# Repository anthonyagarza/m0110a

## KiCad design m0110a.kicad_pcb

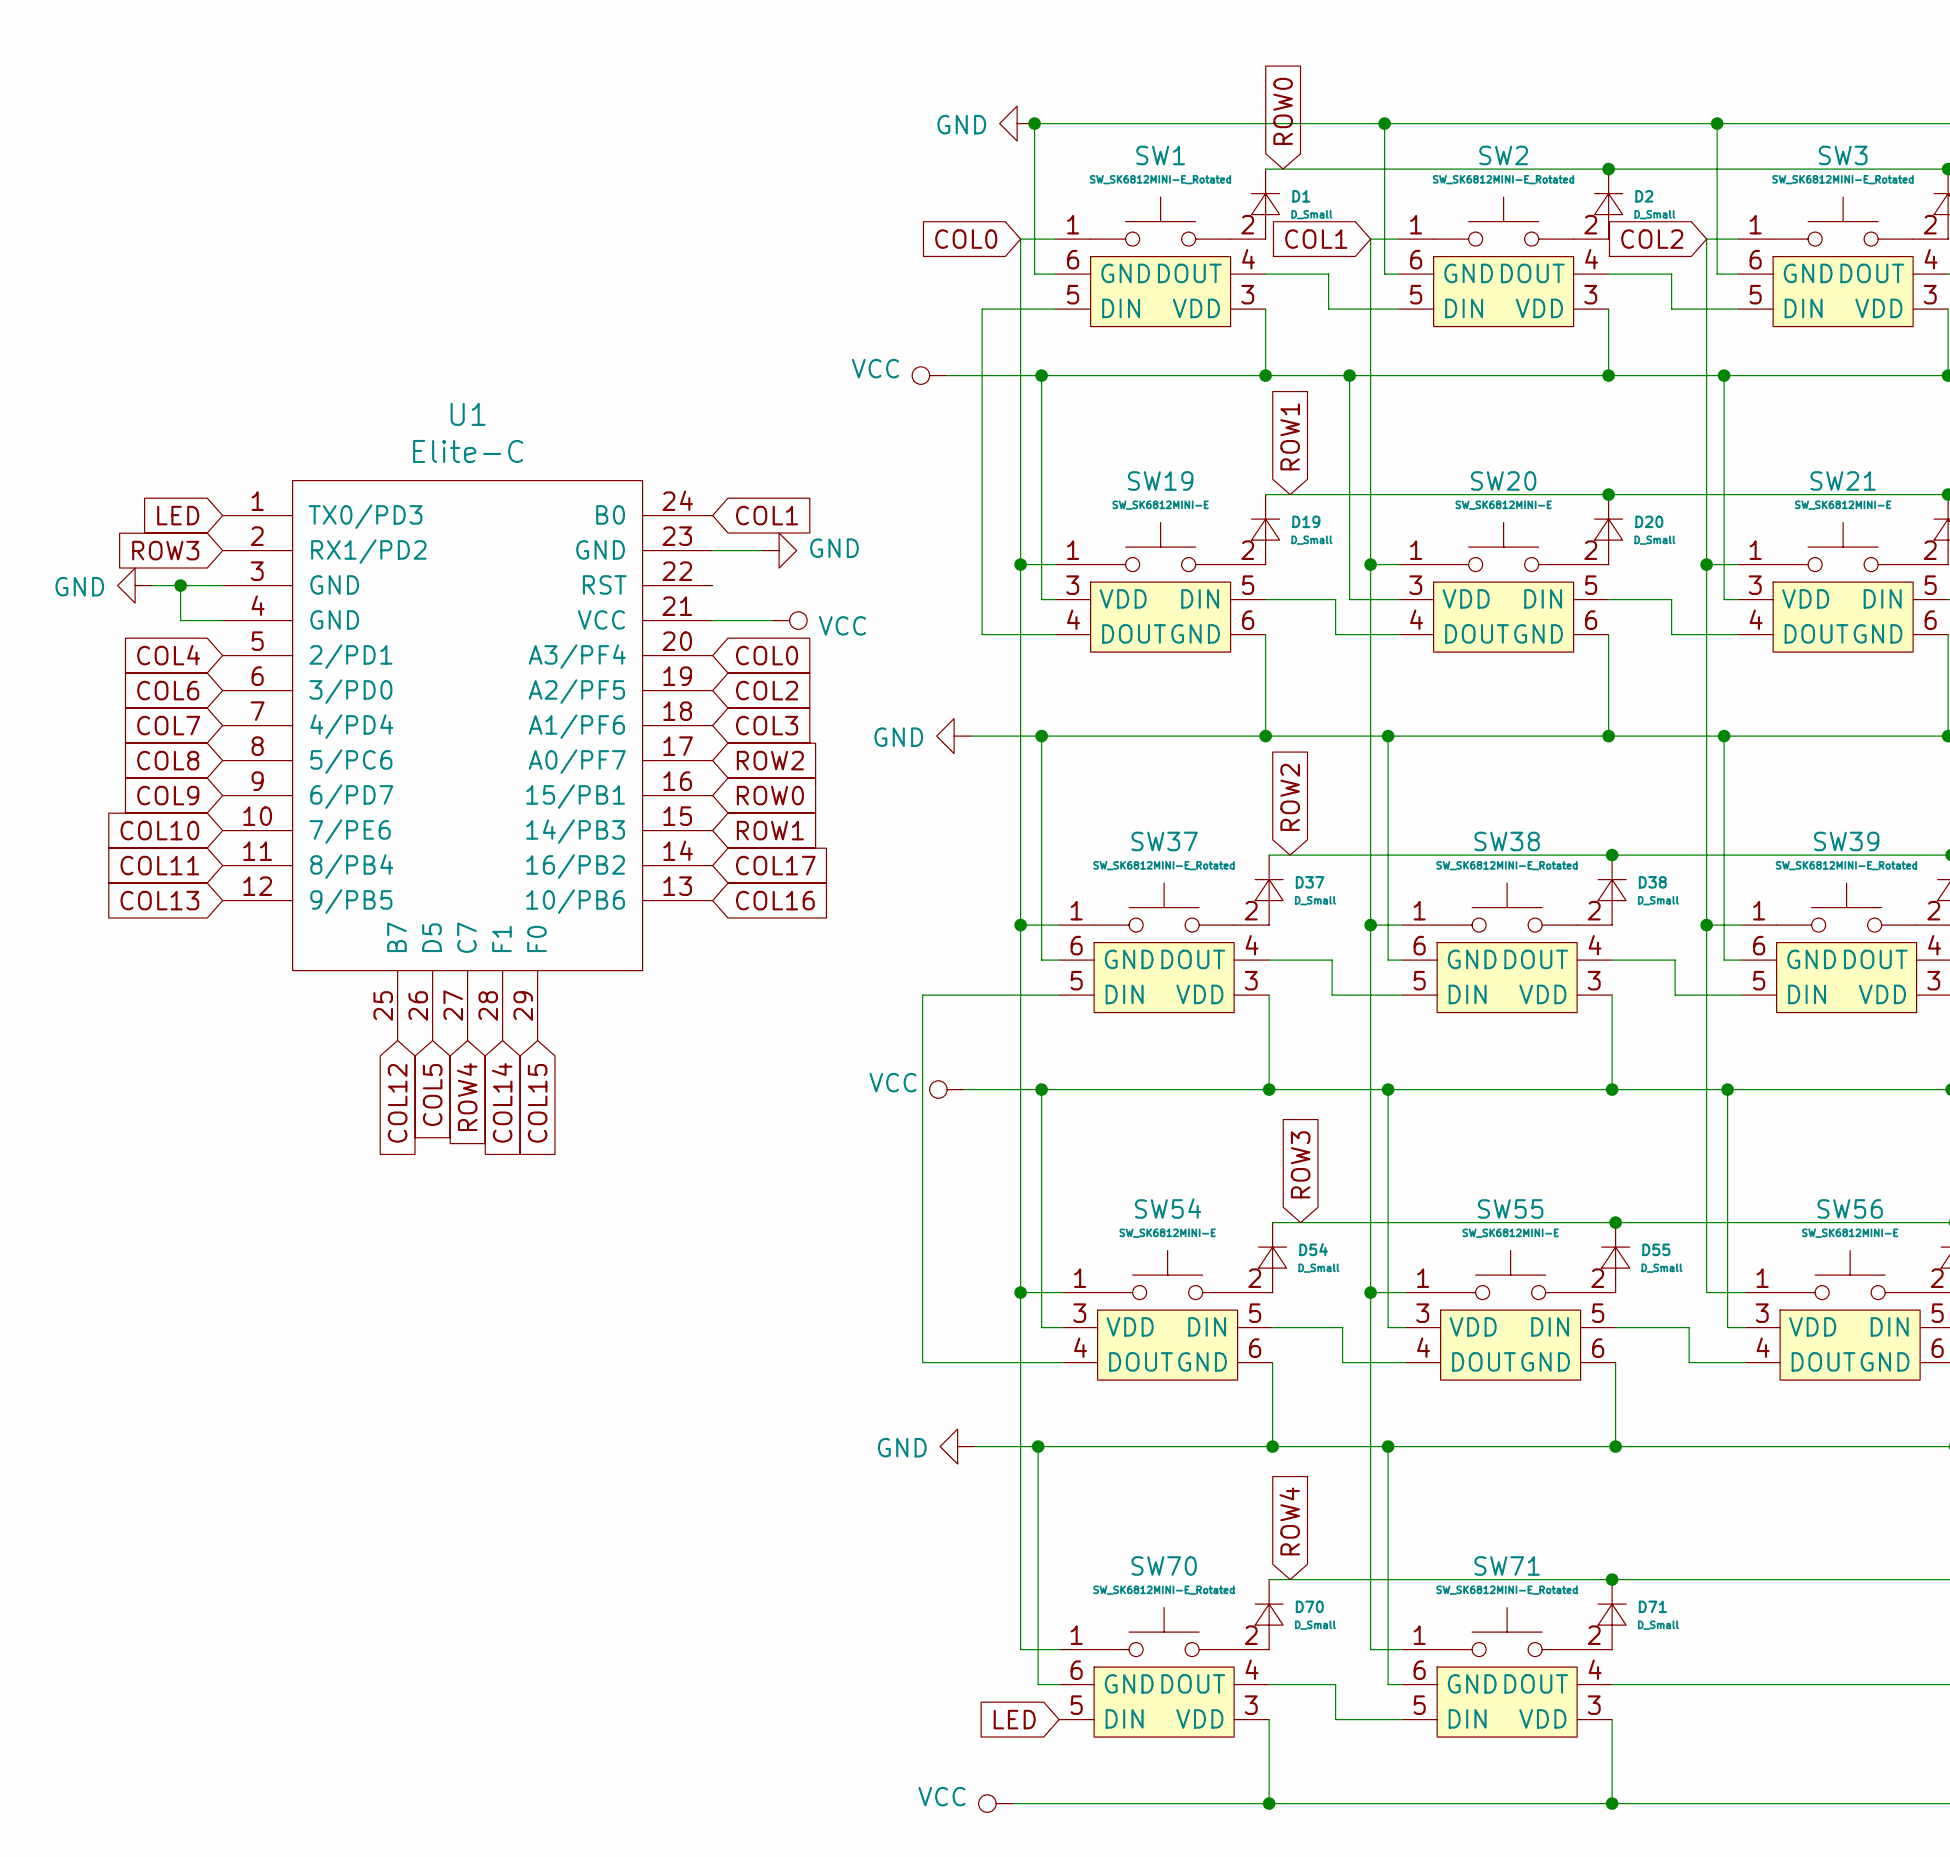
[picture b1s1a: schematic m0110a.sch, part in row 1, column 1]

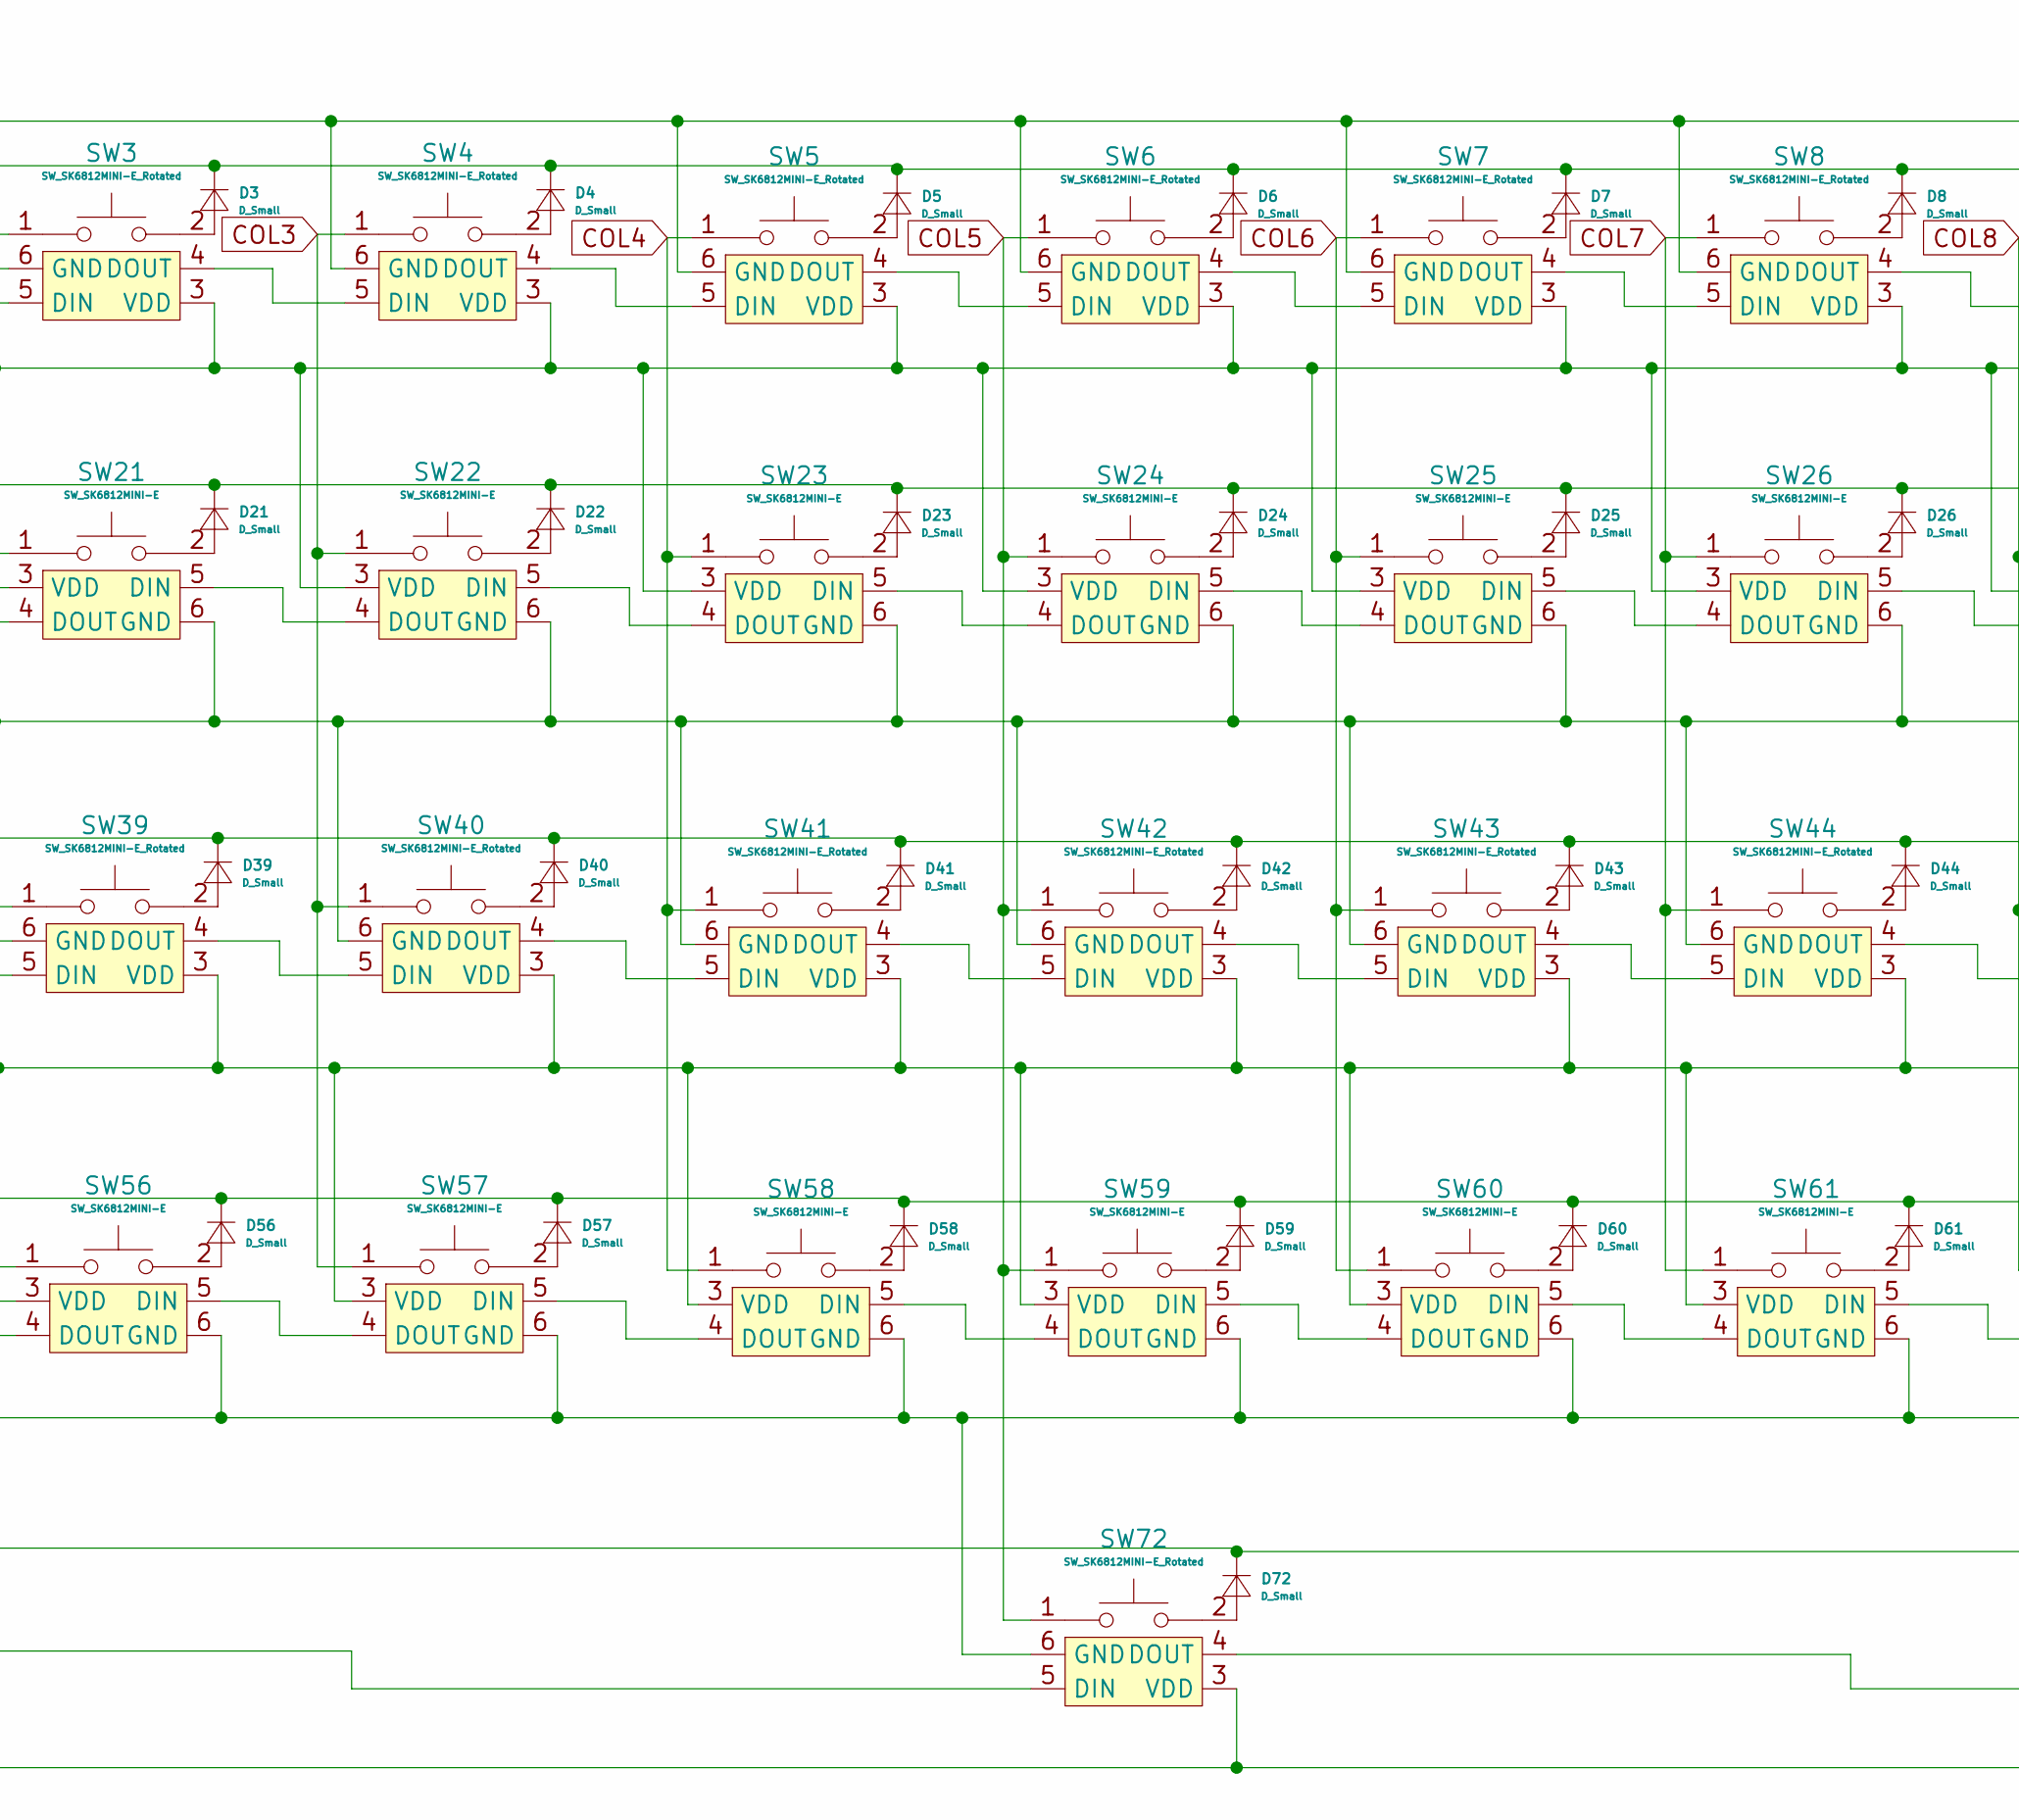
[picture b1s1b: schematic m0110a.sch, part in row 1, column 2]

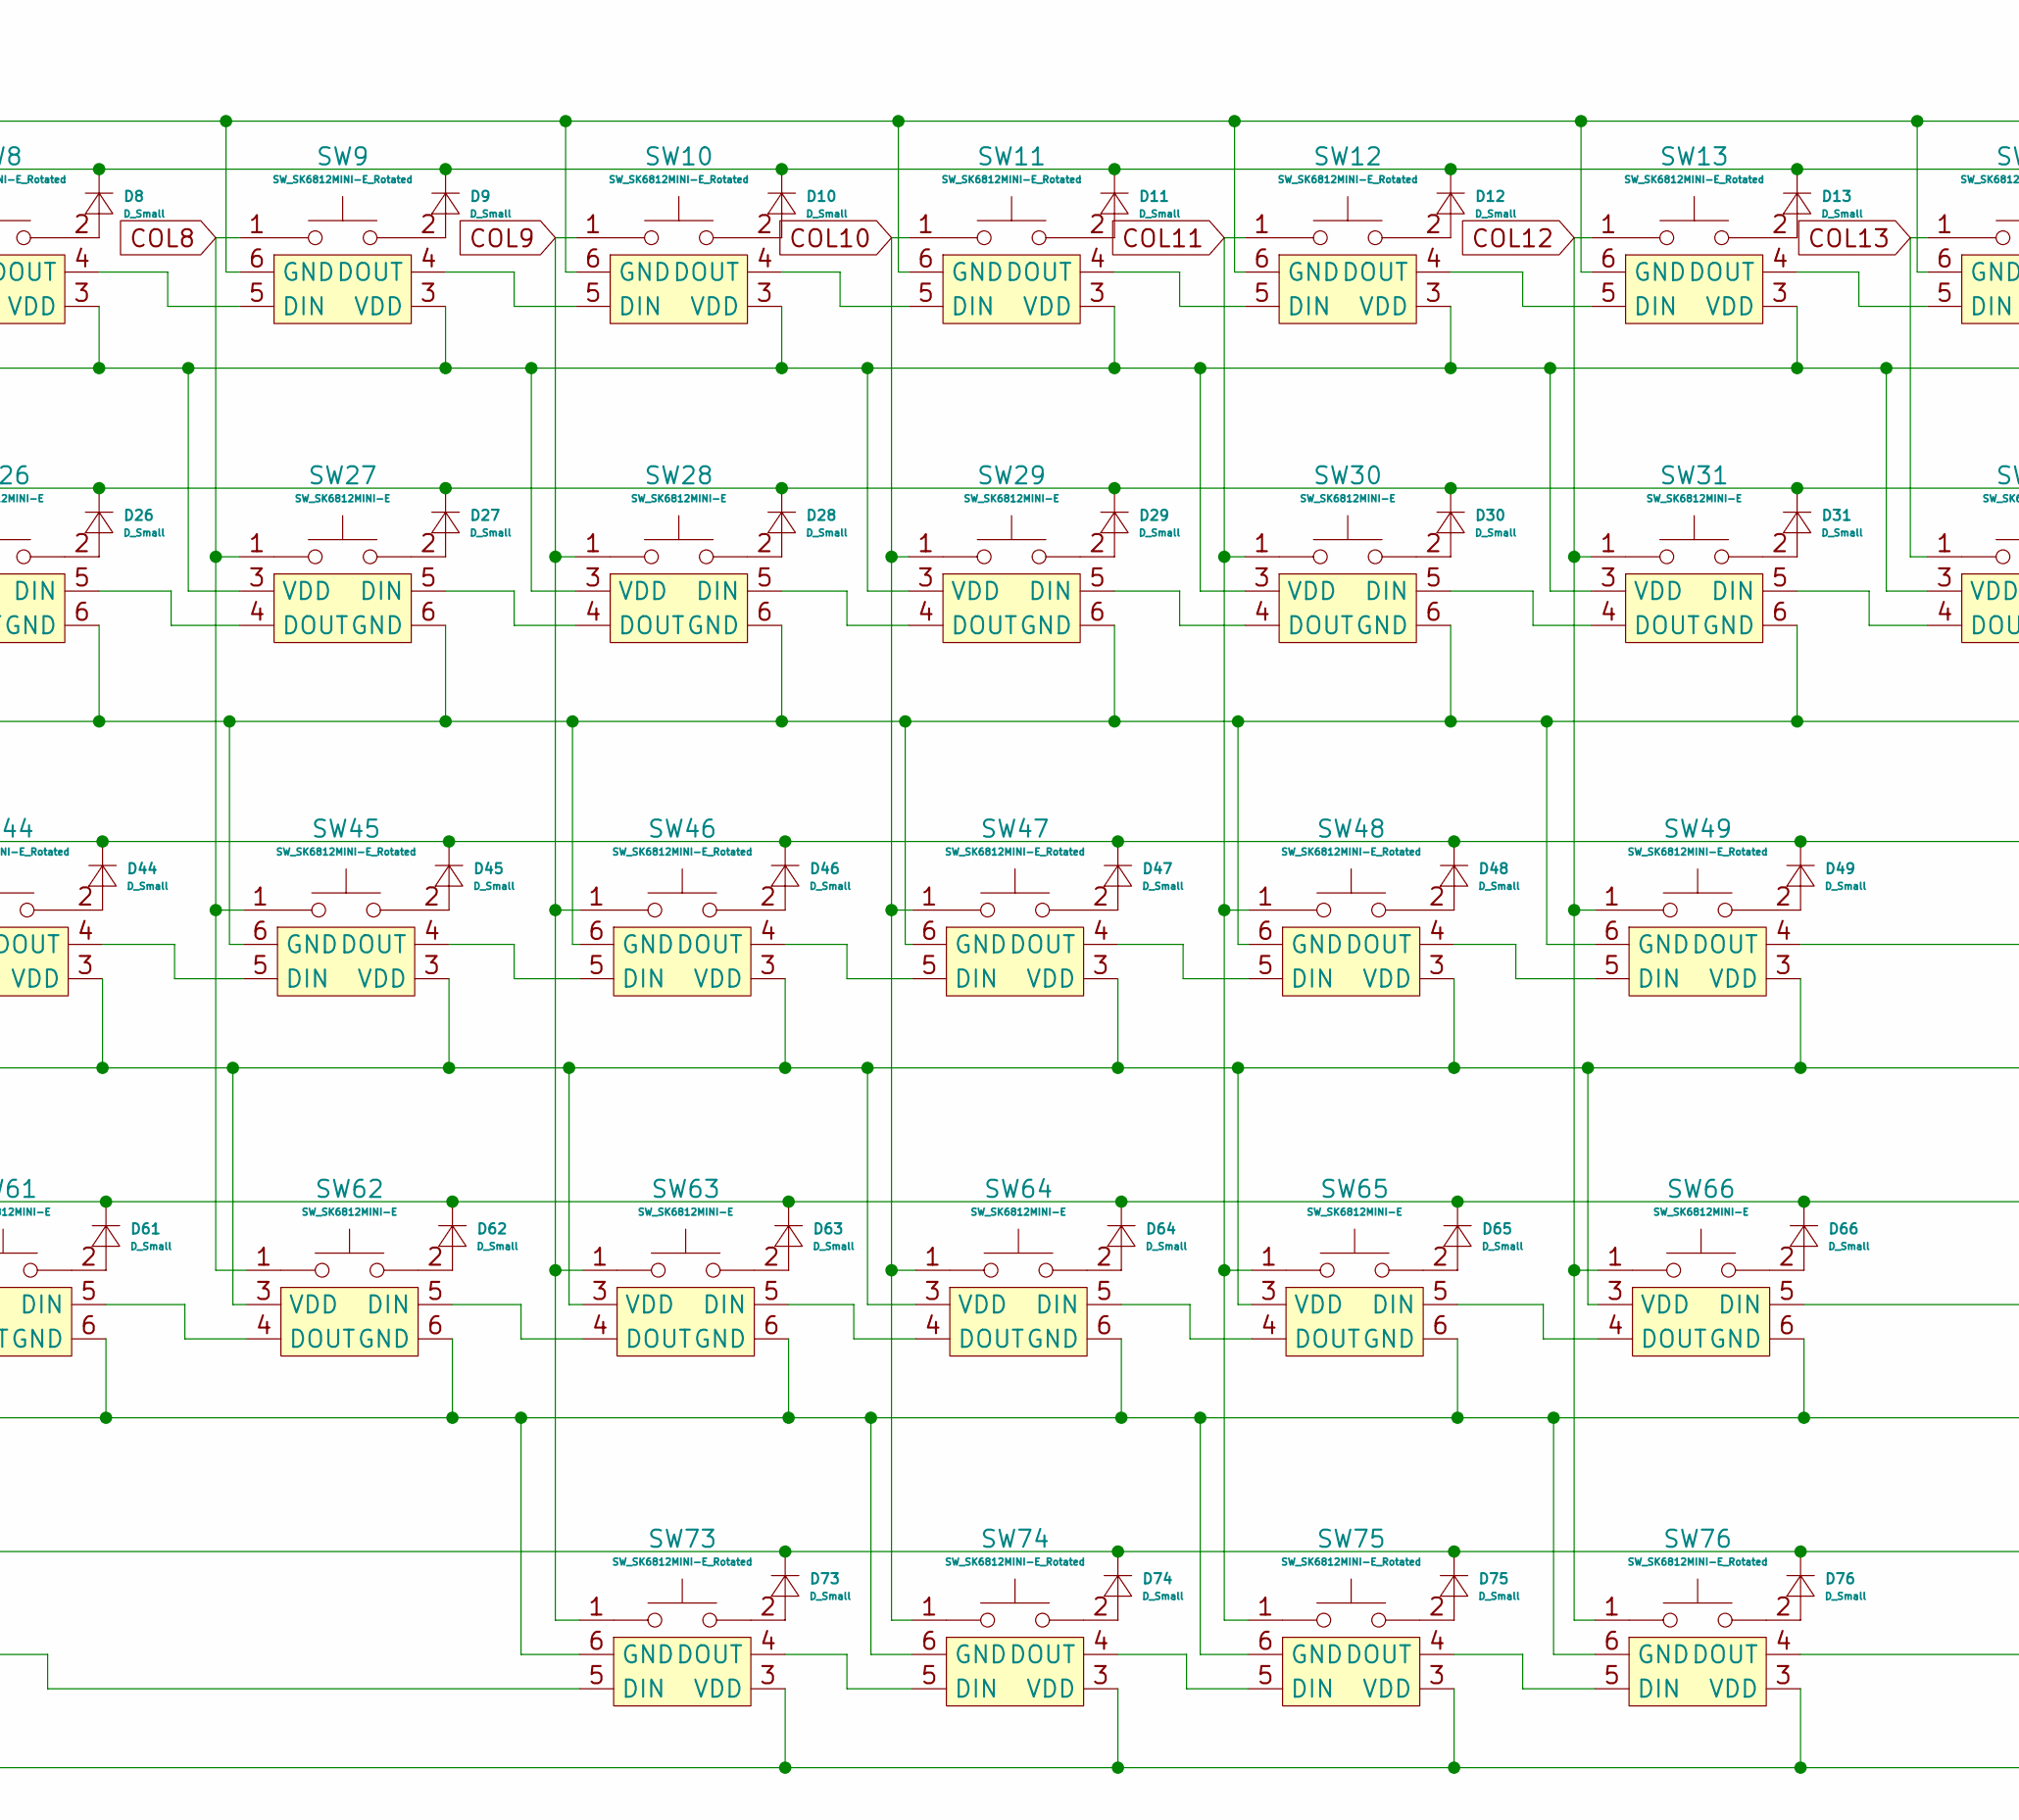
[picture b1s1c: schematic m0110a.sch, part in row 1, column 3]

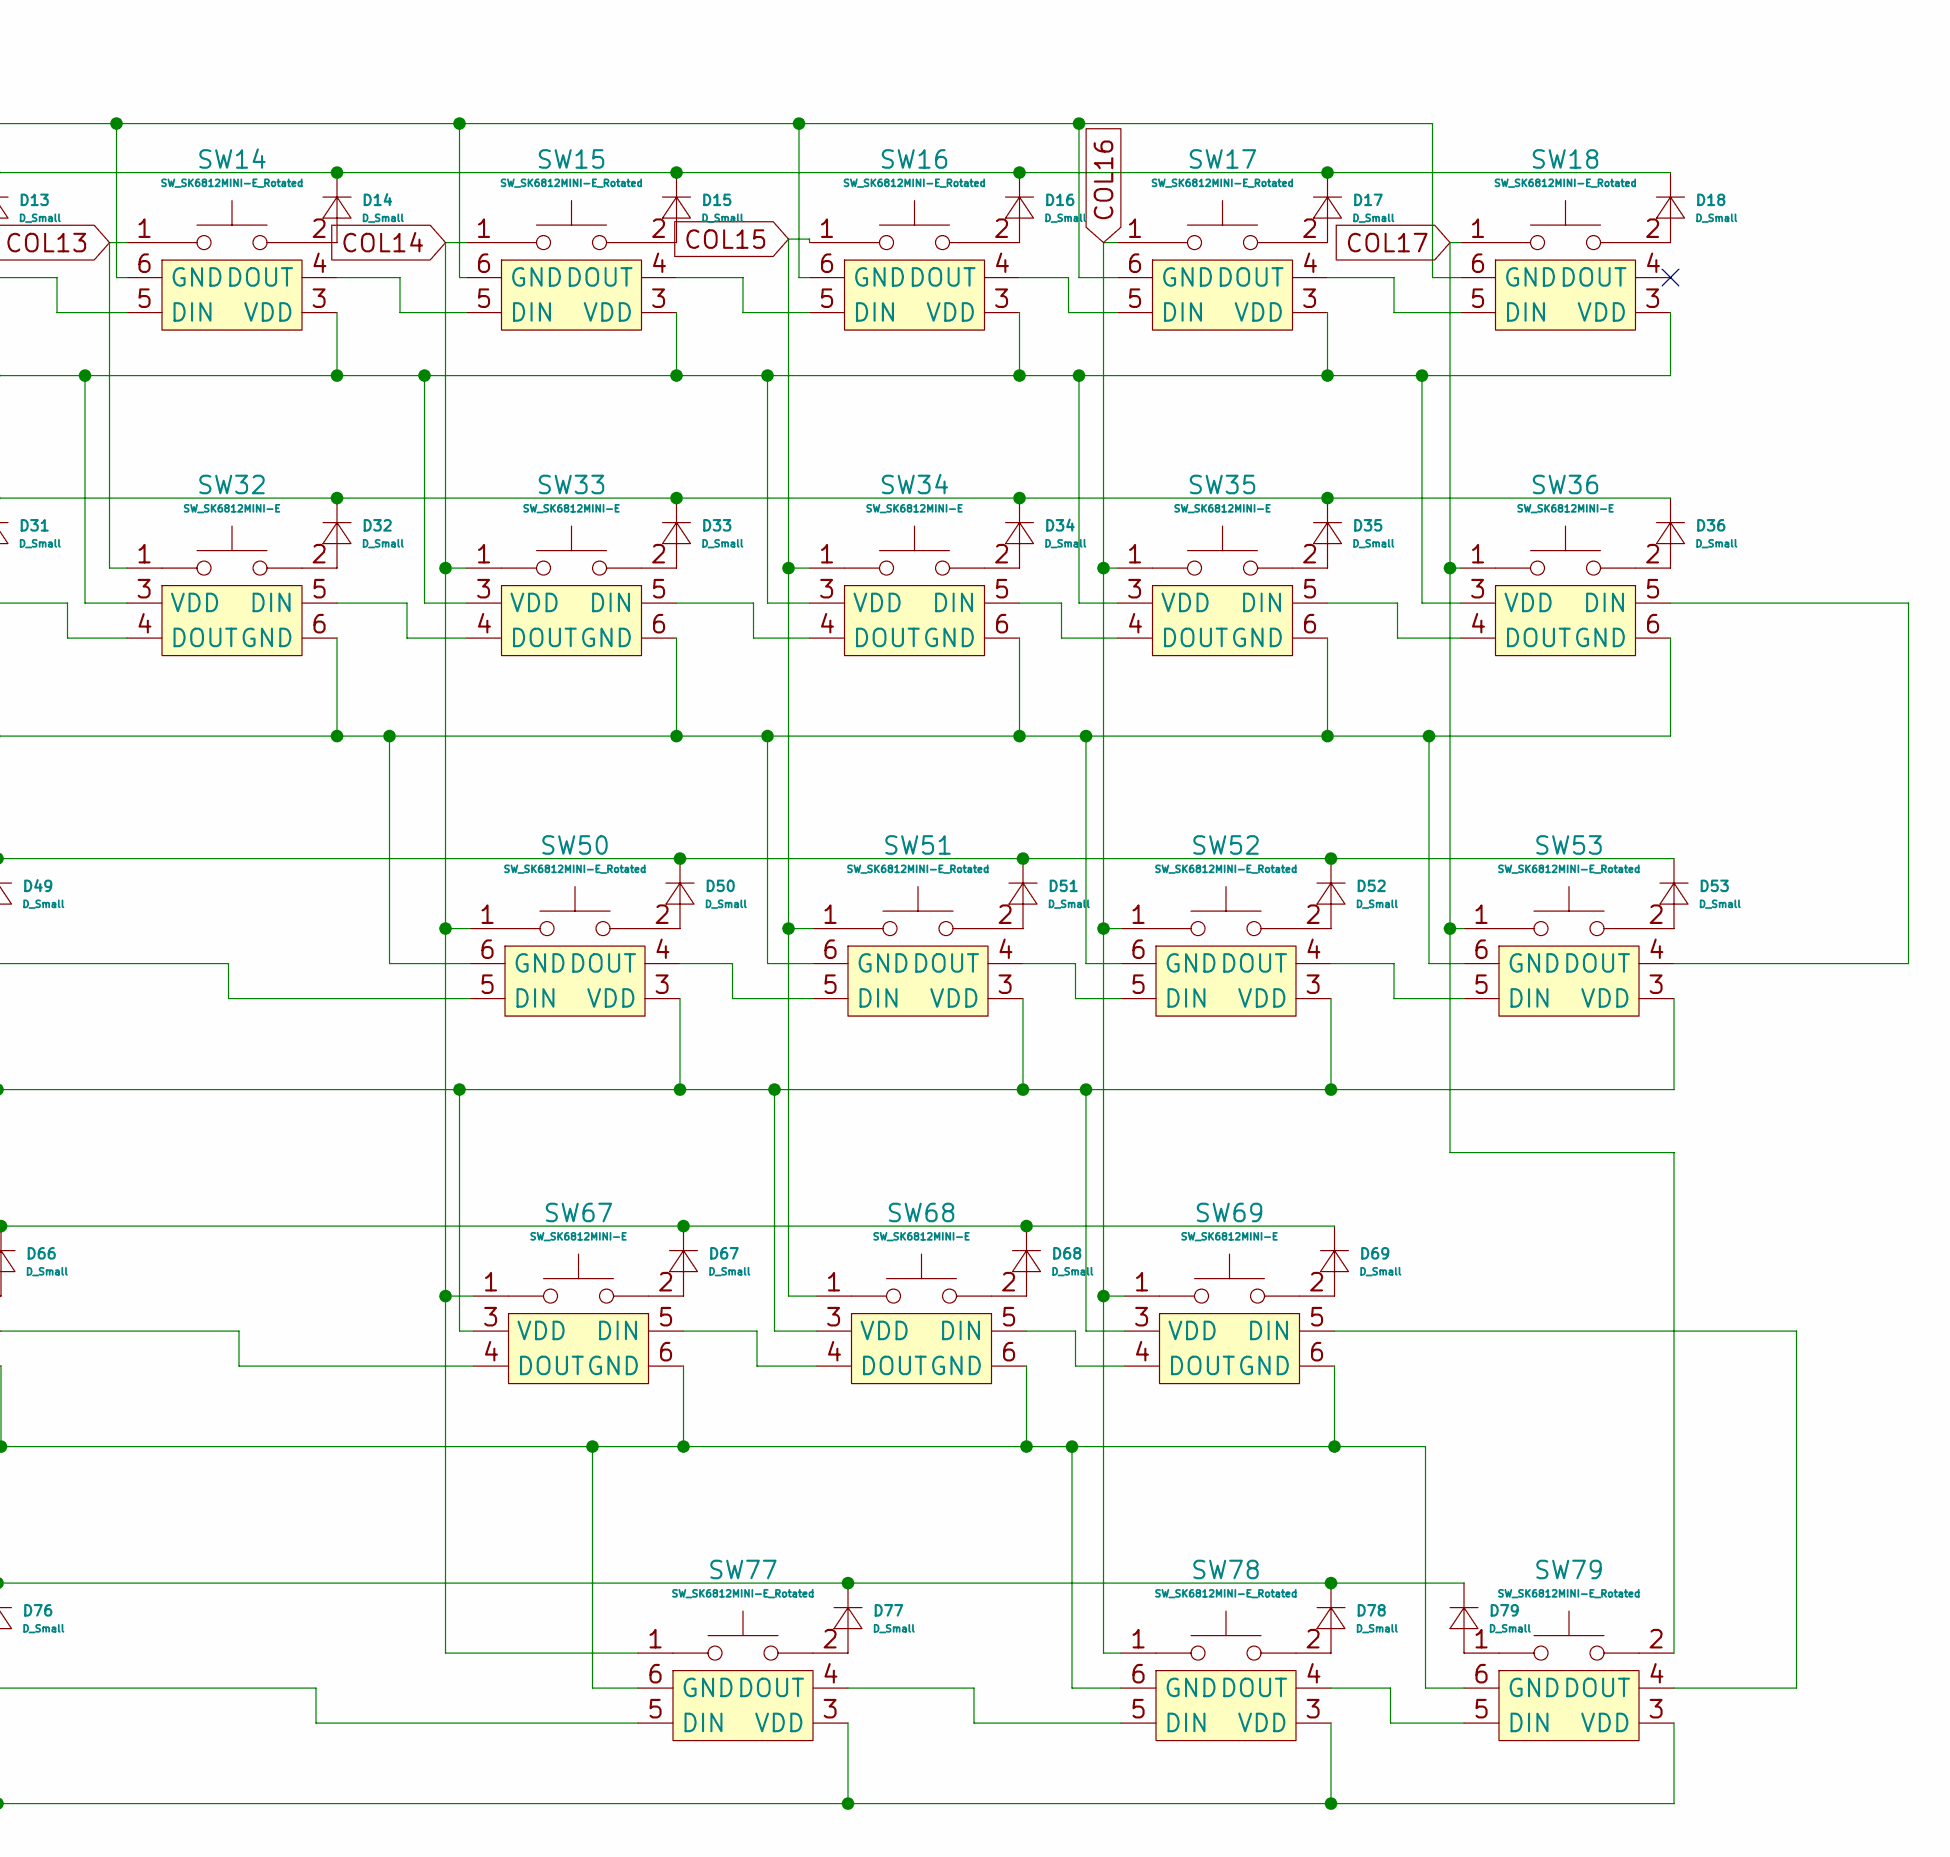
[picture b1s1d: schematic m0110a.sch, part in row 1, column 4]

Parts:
D1, D2, D3, D4, D5, D6, D7, D8, D9, D10, D11, D12, D13, D14, D15, D16, D17, D18, D19, D20, D21, D22, D23, D24, D25, D26, D27, D28, D29, D30, D31, D32, D33, D34, D35, D36, D37, D38, D39, D40, D41, D42, D43, D44, D45, D46, D47, D48, D49, D50, D51, D52, D53, D54, D55, D56, D57, D58, D59, D60, D61, D62, D63, D64, D65, D66, D67, D68, D69, D70, D71, D72, D73, D74, D75, D76, D77, D78, D79: D_Small; Diode
SW1, SW2, SW3, SW4, SW5, SW6, SW7, SW8, SW9, SW10, SW11, SW12, SW13, SW15, SW16, SW17, SW18, SW38, SW39, SW40, SW41, SW42, SW43, SW44, SW45, SW46, SW47, SW48, SW50, SW51, SW52, SW53, SW73, SW74, SW75, SW76, SW78: SW_SK6812MINI-E_Rotated; CherryMX_1.00u_PCB_KailhSocket_LTST-A683CEGBW-Rotated
SW14: SW_SK6812MINI-E_Rotated; CherryMX_1.50u_PCB_KailhSocket_LTST-A683CEGBW-Rotated
SW19: SW_SK6812MINI-E; CherryMX_1.50u_PCB_KailhSocket_LTST-A683CEGBW
SW20, SW21, SW22, SW23, SW24, SW25, SW26, SW27, SW28, SW29, SW30, SW31, SW32, SW33, SW34, SW35, SW36, SW55, SW56, SW57, SW58, SW59, SW60, SW61, SW62, SW63, SW64, SW66, SW67, SW68, SW69: SW_SK6812MINI-E; CherryMX_1.00u_PCB_KailhSocket_LTST-A683CEGBW
SW37, SW49: SW_SK6812MINI-E_Rotated; CherryMX_1.75u_PCB_KailhSocket_LTST-A683CEGBW-Rotated
SW54: SW_SK6812MINI-E; CherryMX_2.25u_PCB_KailhSocket_StabWireBottom_LTST-A683CEGBW
SW65: SW_SK6812MINI-E; CherryMX_1.25u_PCB_KailhSocket_LTST-A683CEGBW
SW70: SW_SK6812MINI-E_Rotated; CherryMX_1.50u_PCB_KailhSocket_LTST-A683CEGBW
SW71, SW77, SW79: SW_SK6812MINI-E_Rotated; CherryMX_2.00u_PCB_KailhSocket_StabWireBottom_LTST-A683CEGB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
SW72: SW_SK6812MINI-E_Rotated; CherryMX_7.00u_PCB_KailhSocket_StabWireBottom_LTST-A683CEGB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
U1: Elite-C

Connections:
COL0: SW1.1, SW19.1, SW37.1, SW54.1, SW70.1, U1.20 (A3/PF4)
COL1: SW2.1, SW20.1, SW38.1, SW55.1, SW71.1, U1.24 (B0)
COL2: SW3.1, SW21.1, SW39.1, SW56.1, U1.19 (A2/PF5)
COL3: SW4.1, SW22.1, SW40.1, SW57.1, U1.18 (A1/PF6)
COL4: SW5.1, SW23.1, SW41.1, SW58.1, U1.5 (2/PD1)
COL5: SW6.1, SW24.1, SW42.1, SW59.1, SW72.1, U1.26 (D5)
COL6: SW7.1, SW25.1, SW43.1, SW60.1, U1.6 (3/PD0)
COL7: SW8.1, SW26.1, SW44.1, SW61.1, U1.7 (4/PD4)
COL8: SW9.1, SW27.1, SW45.1, SW62.1, U1.8 (5/PC6)
COL9: SW10.1, SW28.1, SW46.1, SW63.1, SW73.1, U1.9 (6/PD7)
COL10: SW11.1, SW29.1, SW47.1, SW64.1, SW74.1, U1.10 (7/PE6)
COL11: SW12.1, SW30.1, SW48.1, SW65.1, SW75.1, U1.11 (8/PB4)
COL12: SW13.1, SW31.1, SW49.1, SW66.1, SW76.1, U1.25 (B7)
COL13: SW14.1, SW32.1, U1.12 (9/PB5)
COL14: SW15.1, SW33.1, SW50.1, SW67.1, SW77.1, U1.28 (F1)
COL15: SW16.1, SW34.1, SW51.1, SW68.1, U1.29 (F0)
COL16: SW17.1, SW35.1, SW52.1, SW69.1, SW78.1, U1.13 (10/PB6)
COL17: SW18.1, SW36.1, SW53.1, SW79.2, U1.14 (16/PB2)
GND: SW1.6 (GND), SW2.6 (GND), SW3.6 (GND), SW4.6 (GND), SW5.6 (GND), SW6.6 (GND), SW7.6 (GND), SW8.6 (GND), SW9.6 (GND), SW10.6 (GND), SW11.6 (GND), SW12.6 (GND), SW13.6 (GND), SW14.6 (GND), SW15.6 (GND), SW16.6 (GND), SW17.6 (GND), SW18.6 (GND), SW19.6 (GND), SW20.6 (GND), SW21.6 (GND), SW22.6 (GND), SW23.6 (GND), SW24.6 (GND), SW25.6 (GND), SW26.6 (GND), SW27.6 (GND), SW28.6 (GND), SW29.6 (GND), SW30.6 (GND), SW31.6 (GND), SW32.6 (GND), SW33.6 (GND), SW34.6 (GND), SW35.6 (GND), SW36.6 (GND), SW37.6 (GND), SW38.6 (GND), SW39.6 (GND), SW40.6 (GND), SW41.6 (GND), SW42.6 (GND), SW43.6 (GND), SW44.6 (GND), SW45.6 (GND), SW46.6 (GND), SW47.6 (GND), SW48.6 (GND), SW49.6 (GND), SW50.6 (GND), SW51.6 (GND), SW52.6 (GND), SW53.6 (GND), SW54.6 (GND), SW55.6 (GND), SW56.6 (GND), SW57.6 (GND), SW58.6 (GND), SW59.6 (GND), SW60.6 (GND), SW61.6 (GND), SW62.6 (GND), SW63.6 (GND), SW64.6 (GND), SW65.6 (GND), SW66.6 (GND), SW67.6 (GND), SW68.6 (GND), SW69.6 (GND), SW70.6 (GND), SW71.6 (GND), SW72.6 (GND), SW73.6 (GND), SW74.6 (GND), SW75.6 (GND), SW76.6 (GND), SW77.6 (GND), SW78.6 (GND), SW79.6 (GND), U1.3 (GND), U1.4 (GND), U1.23 (GND)
LED: SW70.5 (DIN), U1.1 (TX0/PD3)
unnamed: D1.2 (A), SW1.2
unnamed: D2.2 (A), SW2.2
unnamed: D3.2 (A), SW3.2
unnamed: D4.2 (A), SW4.2
unnamed: D5.2 (A), SW5.2
unnamed: D6.2 (A), SW6.2
unnamed: D7.2 (A), SW7.2
unnamed: D8.2 (A), SW8.2
unnamed: D9.2 (A), SW9.2
unnamed: D10.2 (A), SW10.2
unnamed: D11.2 (A), SW11.2
unnamed: D12.2 (A), SW12.2
unnamed: D13.2 (A), SW13.2
unnamed: D14.2 (A), SW14.2
unnamed: D15.2 (A), SW15.2
unnamed: D16.2 (A), SW16.2
unnamed: D17.2 (A), SW17.2
unnamed: D18.2 (A), SW18.2
unnamed: D19.2 (A), SW19.2
unnamed: D20.2 (A), SW20.2
unnamed: D21.2 (A), SW21.2
unnamed: D22.2 (A), SW22.2
unnamed: D23.2 (A), SW23.2
unnamed: D24.2 (A), SW24.2
unnamed: D25.2 (A), SW25.2
unnamed: D26.2 (A), SW26.2
unnamed: D27.2 (A), SW27.2
unnamed: D28.2 (A), SW28.2
unnamed: D29.2 (A), SW29.2
unnamed: D30.2 (A), SW30.2
unnamed: D31.2 (A), SW31.2
unnamed: D32.2 (A), SW32.2
unnamed: D33.2 (A), SW33.2
unnamed: D34.2 (A), SW34.2
unnamed: D35.2 (A), SW35.2
unnamed: D36.2 (A), SW36.2
unnamed: D37.2 (A), SW37.2
unnamed: D38.2 (A), SW38.2
unnamed: D39.2 (A), SW39.2
unnamed: D40.2 (A), SW40.2
unnamed: D41.2 (A), SW41.2
unnamed: D42.2 (A), SW42.2
unnamed: D43.2 (A), SW43.2
unnamed: D44.2 (A), SW44.2
unnamed: D45.2 (A), SW45.2
unnamed: D46.2 (A), SW46.2
unnamed: D47.2 (A), SW47.2
unnamed: D48.2 (A), SW48.2
unnamed: D49.2 (A), SW49.2
unnamed: D50.2 (A), SW50.2
unnamed: D51.2 (A), SW51.2
unnamed: D52.2 (A), SW52.2
unnamed: D53.2 (A), SW53.2
unnamed: D54.2 (A), SW54.2
unnamed: D55.2 (A), SW55.2
unnamed: D56.2 (A), SW56.2
unnamed: D57.2 (A), SW57.2
unnamed: D58.2 (A), SW58.2
unnamed: D59.2 (A), SW59.2
unnamed: D60.2 (A), SW60.2
unnamed: D61.2 (A), SW61.2
unnamed: D62.2 (A), SW62.2
unnamed: D63.2 (A), SW63.2
unnamed: D64.2 (A), SW64.2
unnamed: D65.2 (A), SW65.2
unnamed: D66.2 (A), SW66.2
unnamed: D67.2 (A), SW67.2
unnamed: D68.2 (A), SW68.2
unnamed: D69.2 (A), SW69.2
unnamed: D70.2 (A), SW70.2
unnamed: D71.2 (A), SW71.2
unnamed: D72.2 (A), SW72.2
unnamed: D73.2 (A), SW73.2
unnamed: D74.2 (A), SW74.2
unnamed: D75.2 (A), SW75.2
unnamed: D76.2 (A), SW76.2
unnamed: D77.2 (A), SW77.2
unnamed: D78.2 (A), SW78.2
unnamed: D79.2 (A), SW79.1
unnamed: SW1.4 (DOUT), SW2.5 (DIN)
unnamed: SW1.5 (DIN), SW19.4 (DOUT)
unnamed: SW2.4 (DOUT), SW3.5 (DIN)
unnamed: SW3.4 (DOUT), SW4.5 (DIN)
unnamed: SW4.4 (DOUT), SW5.5 (DIN)
unnamed: SW5.4 (DOUT), SW6.5 (DIN)
unnamed: SW6.4 (DOUT), SW7.5 (DIN)
unnamed: SW7.4 (DOUT), SW8.5 (DIN)
unnamed: SW8.4 (DOUT), SW9.5 (DIN)
unnamed: SW10.4 (DOUT), SW11.5 (DIN)
unnamed: SW9.4 (DOUT), SW10.5 (DIN)
unnamed: SW11.4 (DOUT), SW12.5 (DIN)
unnamed: SW12.4 (DOUT), SW13.5 (DIN)
unnamed: SW13.4 (DOUT), SW14.5 (DIN)
unnamed: SW14.4 (DOUT), SW15.5 (DIN)
unnamed: SW15.4 (DOUT), SW16.5 (DIN)
unnamed: SW16.4 (DOUT), SW17.5 (DIN)
unnamed: SW17.4 (DOUT), SW18.5 (DIN)
unnamed: SW19.5 (DIN), SW20.4 (DOUT)
unnamed: SW20.5 (DIN), SW21.4 (DOUT)
unnamed: SW21.5 (DIN), SW22.4 (DOUT)
unnamed: SW22.5 (DIN), SW23.4 (DOUT)
unnamed: SW23.5 (DIN), SW24.4 (DOUT)
unnamed: SW24.5 (DIN), SW25.4 (DOUT)
unnamed: SW25.5 (DIN), SW26.4 (DOUT)
unnamed: SW26.5 (DIN), SW27.4 (DOUT)
unnamed: SW27.5 (DIN), SW28.4 (DOUT)
unnamed: SW28.5 (DIN), SW29.4 (DOUT)
unnamed: SW29.5 (DIN), SW30.4 (DOUT)
unnamed: SW30.5 (DIN), SW31.4 (DOUT)
unnamed: SW31.5 (DIN), SW32.4 (DOUT)
unnamed: SW32.5 (DIN), SW33.4 (DOUT)
unnamed: SW33.5 (DIN), SW34.4 (DOUT)
unnamed: SW34.5 (DIN), SW35.4 (DOUT)
unnamed: SW35.5 (DIN), SW36.4 (DOUT)
unnamed: SW36.5 (DIN), SW53.4 (DOUT)
unnamed: SW37.4 (DOUT), SW38.5 (DIN)
unnamed: SW37.5 (DIN), SW54.4 (DOUT)
unnamed: SW38.4 (DOUT), SW39.5 (DIN)
unnamed: SW39.4 (DOUT), SW40.5 (DIN)
unnamed: SW40.4 (DOUT), SW41.5 (DIN)
unnamed: SW41.4 (DOUT), SW42.5 (DIN)
unnamed: SW42.4 (DOUT), SW43.5 (DIN)
unnamed: SW43.4 (DOUT), SW44.5 (DIN)
unnamed: SW44.4 (DOUT), SW45.5 (DIN)
unnamed: SW45.4 (DOUT), SW46.5 (DIN)
unnamed: SW46.4 (DOUT), SW47.5 (DIN)
unnamed: SW47.4 (DOUT), SW48.5 (DIN)
unnamed: SW48.4 (DOUT), SW49.5 (DIN)
unnamed: SW49.4 (DOUT), SW50.5 (DIN)
unnamed: SW50.4 (DOUT), SW51.5 (DIN)
unnamed: SW51.4 (DOUT), SW52.5 (DIN)
unnamed: SW52.4 (DOUT), SW53.5 (DIN)
unnamed: SW54.5 (DIN), SW55.4 (DOUT)
unnamed: SW55.5 (DIN), SW56.4 (DOUT)
unnamed: SW56.5 (DIN), SW57.4 (DOUT)
unnamed: SW57.5 (DIN), SW58.4 (DOUT)
unnamed: SW58.5 (DIN), SW59.4 (DOUT)
unnamed: SW59.5 (DIN), SW60.4 (DOUT)
unnamed: SW60.5 (DIN), SW61.4 (DOUT)
unnamed: SW61.5 (DIN), SW62.4 (DOUT)
unnamed: SW62.5 (DIN), SW63.4 (DOUT)
unnamed: SW63.5 (DIN), SW64.4 (DOUT)
unnamed: SW64.5 (DIN), SW65.4 (DOUT)
unnamed: SW65.5 (DIN), SW66.4 (DOUT)
unnamed: SW66.5 (DIN), SW67.4 (DOUT)
unnamed: SW67.5 (DIN), SW68.4 (DOUT)
unnamed: SW68.5 (DIN), SW69.4 (DOUT)
unnamed: SW69.5 (DIN), SW79.4 (DOUT)
unnamed: SW70.4 (DOUT), SW71.5 (DIN)
unnamed: SW71.4 (DOUT), SW72.5 (DIN)
unnamed: SW72.4 (DOUT), SW73.5 (DIN)
unnamed: SW73.4 (DOUT), SW74.5 (DIN)
unnamed: SW74.4 (DOUT), SW75.5 (DIN)
unnamed: SW75.4 (DOUT), SW76.5 (DIN)
unnamed: SW76.4 (DOUT), SW77.5 (DIN)
unnamed: SW77.4 (DOUT), SW78.5 (DIN)
unnamed: SW78.4 (DOUT), SW79.5 (DIN)
ROW0: D1.1 (K), D2.1 (K), D3.1 (K), D4.1 (K), D5.1 (K), D6.1 (K), D7.1 (K), D8.1 (K), D9.1 (K), D10.1 (K), D11.1 (K), D12.1 (K), D13.1 (K), D14.1 (K), D15.1 (K), D16.1 (K), D17.1 (K), D18.1 (K), U1.16 (15/PB1)
ROW1: D19.1 (K), D20.1 (K), D21.1 (K), D22.1 (K), D23.1 (K), D24.1 (K), D25.1 (K), D26.1 (K), D27.1 (K), D28.1 (K), D29.1 (K), D30.1 (K), D31.1 (K), D32.1 (K), D33.1 (K), D34.1 (K), D35.1 (K), D36.1 (K), U1.15 (14/PB3)
ROW2: D37.1 (K), D38.1 (K), D39.1 (K), D40.1 (K), D41.1 (K), D42.1 (K), D43.1 (K), D44.1 (K), D45.1 (K), D46.1 (K), D47.1 (K), D48.1 (K), D49.1 (K), D50.1 (K), D51.1 (K), D52.1 (K), D53.1 (K), U1.17 (A0/PF7)
ROW3: D54.1 (K), D55.1 (K), D56.1 (K), D57.1 (K), D58.1 (K), D59.1 (K), D60.1 (K), D61.1 (K), D62.1 (K), D63.1 (K), D64.1 (K), D65.1 (K), D66.1 (K), D67.1 (K), D68.1 (K), D69.1 (K), U1.2 (RX1/PD2)
ROW4: D70.1 (K), D71.1 (K), D72.1 (K), D73.1 (K), D74.1 (K), D75.1 (K), D76.1 (K), D77.1 (K), D78.1 (K), D79.1 (K), U1.27 (C7)
VCC: SW1.3 (VDD), SW2.3 (VDD), SW3.3 (VDD), SW4.3 (VDD), SW5.3 (VDD), SW6.3 (VDD), SW7.3 (VDD), SW8.3 (VDD), SW9.3 (VDD), SW10.3 (VDD), SW11.3 (VDD), SW12.3 (VDD), SW13.3 (VDD), SW14.3 (VDD), SW15.3 (VDD), SW16.3 (VDD), SW17.3 (VDD), SW18.3 (VDD), SW19.3 (VDD), SW20.3 (VDD), SW21.3 (VDD), SW22.3 (VDD), SW23.3 (VDD), SW24.3 (VDD), SW25.3 (VDD), SW26.3 (VDD), SW27.3 (VDD), SW28.3 (VDD), SW29.3 (VDD), SW30.3 (VDD), SW31.3 (VDD), SW32.3 (VDD), SW33.3 (VDD), SW34.3 (VDD), SW35.3 (VDD), SW36.3 (VDD), SW37.3 (VDD), SW38.3 (VDD), SW39.3 (VDD), SW40.3 (VDD), SW41.3 (VDD), SW42.3 (VDD), SW43.3 (VDD), SW44.3 (VDD), SW45.3 (VDD), SW46.3 (VDD), SW47.3 (VDD), SW48.3 (VDD), SW49.3 (VDD), SW50.3 (VDD), SW51.3 (VDD), SW52.3 (VDD), SW53.3 (VDD), SW54.3 (VDD), SW55.3 (VDD), SW56.3 (VDD), SW57.3 (VDD), SW58.3 (VDD), SW59.3 (VDD), SW60.3 (VDD), SW61.3 (VDD), SW62.3 (VDD), SW63.3 (VDD), SW64.3 (VDD), SW65.3 (VDD), SW66.3 (VDD), SW67.3 (VDD), SW68.3 (VDD), SW69.3 (VDD), SW70.3 (VDD), SW71.3 (VDD), SW72.3 (VDD), SW73.3 (VDD), SW74.3 (VDD), SW75.3 (VDD), SW76.3 (VDD), SW77.3 (VDD), SW78.3 (VDD), SW79.3 (VDD), U1.21 (VCC)

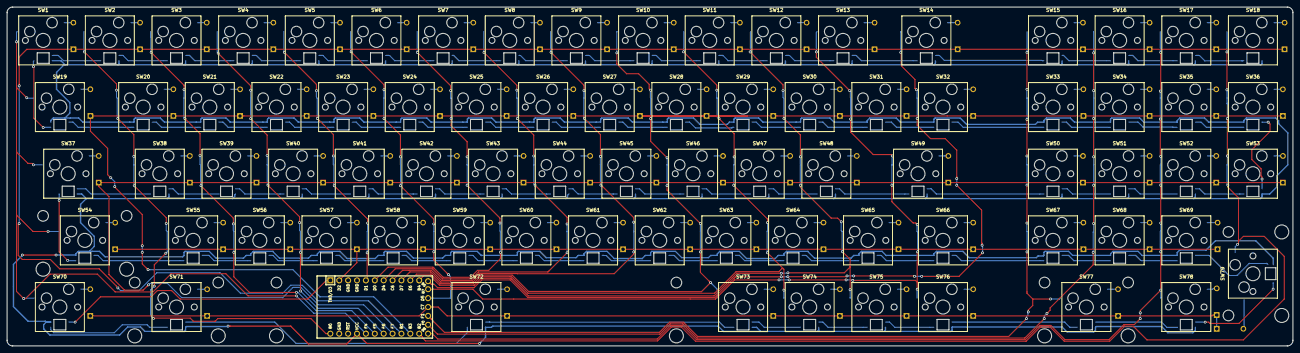
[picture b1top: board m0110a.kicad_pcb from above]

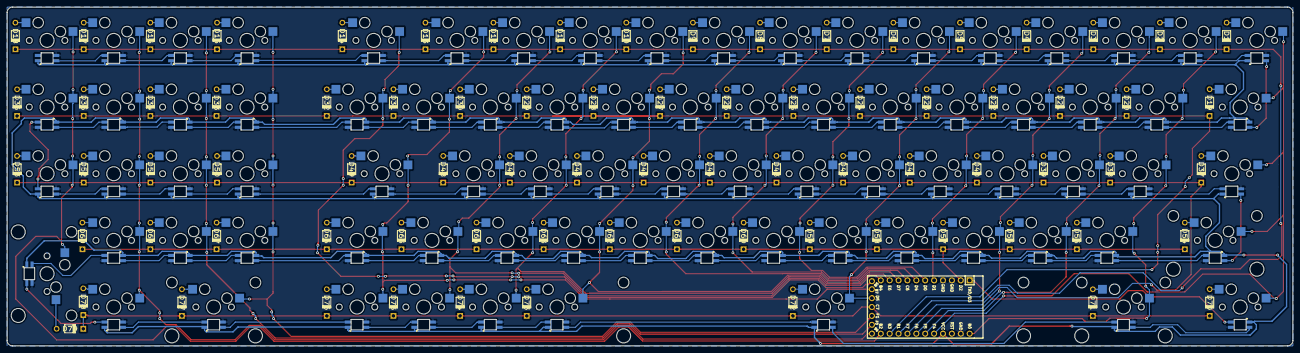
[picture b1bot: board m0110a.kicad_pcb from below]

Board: 2 copper layers, 367.5 x 96.8 mm, 159 parts (80 on the bottom side), 183 nets.

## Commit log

2020-08-16 Add submodules
2020-08-16 add symbol files and foot print files to project
2020-08-16 Add the MCU and required components
2020-08-16 Add USB to schematic
2020-08-16 Add switches and diodes to schematic
2020-08-17 Add matrix wiring to schematic
2020-08-17 add row and colum globals
2020-08-17 added switch references
2020-08-17 Add footprint associations
2020-08-17 start placing footprints
2020-08-18 place main alpha numeric section
2020-08-18 placed number pad
2020-08-19 start placing controller footprints
2020-08-21 replace symbols with hot swap rgb
2020-08-21 connect some of the schematic
2020-08-22 Add row and column schematic
2020-08-22 add rgb led connections left -> right, top -> bottom
2020-08-22 fix foot print associations. place switch foot prints and some diodes
2020-08-22 place number pad 34.5mm away from center of back space
2020-08-22 place diodes
2020-08-22 add pcb edge cuts
2020-08-22 connect first row diodes and rgb data lines
2020-08-23 connect second row's diodes and rgb data lines
2020-08-23 connect third and fourth row diodes and rgb data lines
2020-08-23 add column connections
2020-08-23 connect the data rgb between rows
2020-08-24 start adding capacitors for the LEDs
2020-09-04 Resart to support sk6812mini-e leds for rgb
2020-09-06 connect chematic. start placing footprints
2020-09-06 place footprints and connect leds
2020-09-06 start connecting VCC
2020-09-09 first complete pcb
2020-09-10 Fix DRC errors
2020-09-10 increase corner radius
2020-09-10 fix row 0 and row 1 tracks
2020-09-10 v0.0.1 done
2020-09-11 add row, led data and vcc tracks start columns
2020-09-15 horiontal done
